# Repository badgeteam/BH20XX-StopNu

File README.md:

# Bornhack StopNu project page

For the Bornhack hacker camp we want to build a traffic light system for the
main entrance. The details are still being worked out. This archive will
contain a description and design of all the complete project.

The software repository can be found here:  
https://github.com/badgeteam/stopnu-firmware

The design of the main control board can be found here:
https://github.com/badgeteam/stopnu-hardware

# Directory structure

 * ./documentation: documentation we write and use for designing the StopNu.
 * ./electronics: Wiring and used off the shelf electronic components. 
 * ./mechanical: Mechanical design files and drawings. 
 * ./photos: Photos used to illustrate the design.
 * ./pcb_light: The design of the LED panel (schematic and PCB, CadSoft Eagle and PDF)
# License 

The hardware design is licenced under the "CERN Open Hardware Licence Version 2 - Permissive".

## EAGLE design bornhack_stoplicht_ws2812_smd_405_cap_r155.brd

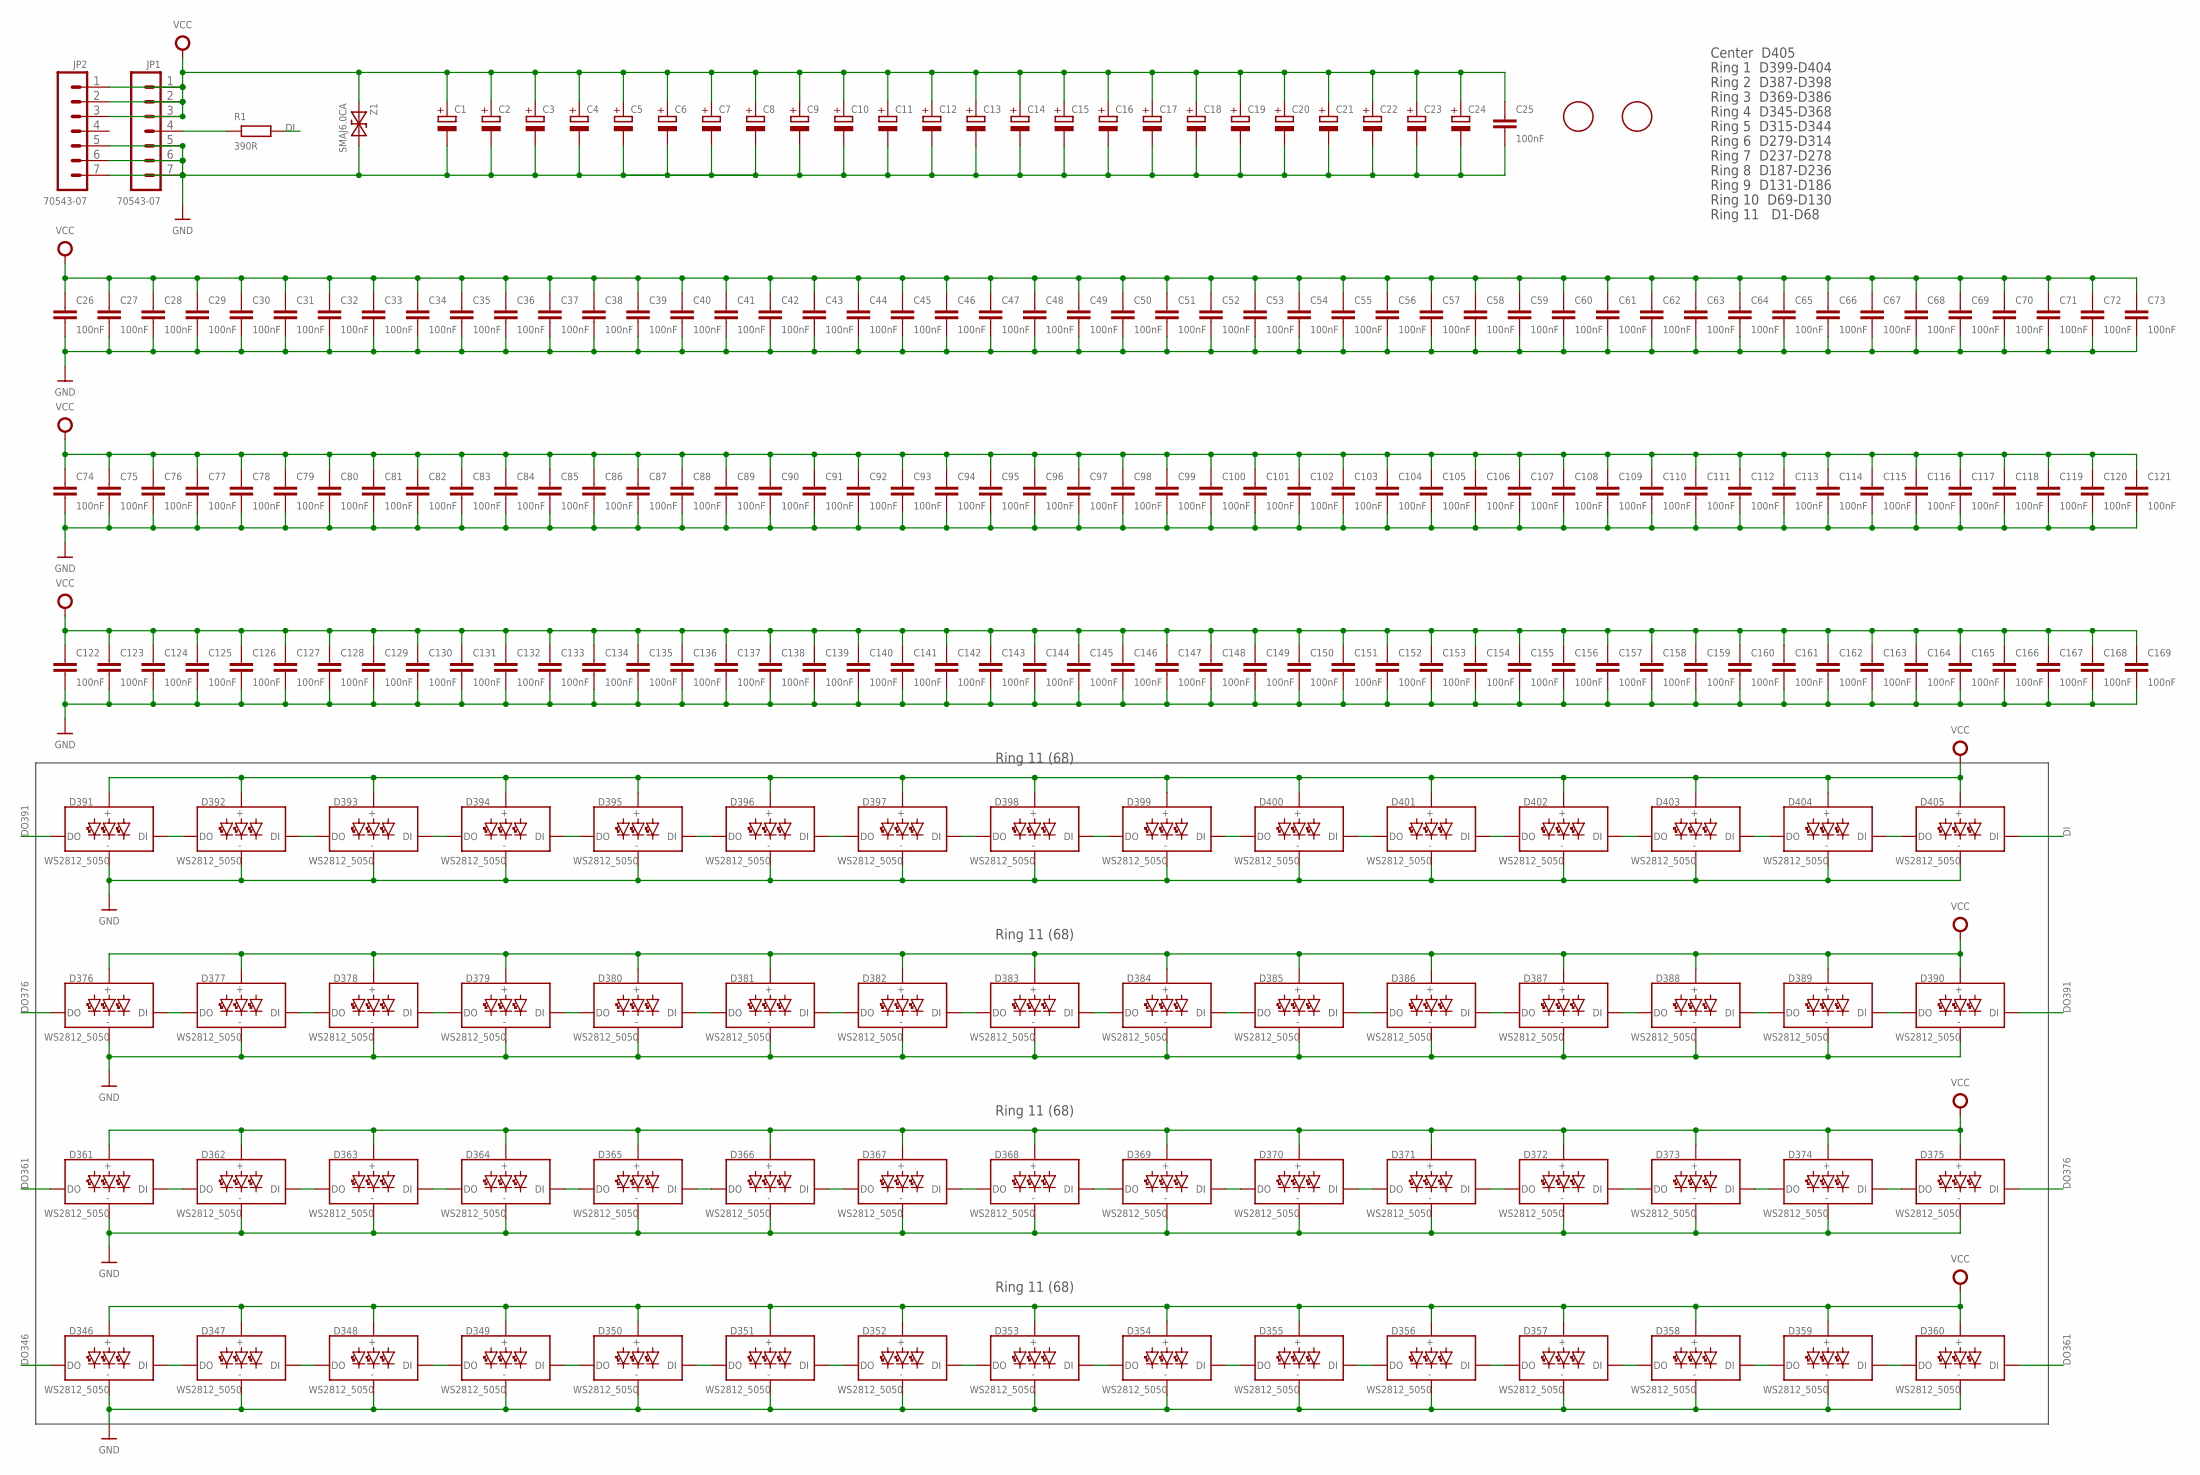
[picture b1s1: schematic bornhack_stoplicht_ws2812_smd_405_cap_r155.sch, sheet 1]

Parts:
C1, C2, C3, C4, C5, C6, C7, C8, C9, C10, C11, C12, C13, C14, C15, C16, C17, C18, C19, C20, C21, C22, C23, C24: CPOL-EUE2.5-6; E2,5-6
C25, C26, C27, C28, C29, C30, C31, C32, C33, C34, C35, C36, C37, C38, C39, C40, C41, C42, C43, C44, C45, C46, C47, C48, C49, C50, C51, C52, C53, C54, C55, C56, C57, C58, C59, C60, C61, C62, C63, C64, C65, C66, C67, C68, C69, C70, C71, C72, C73, C74, C75, C76, C77, C78, C79, C80, C81, C82, C83, C84, C85, C86, C87, C88, C89, C90, C91, C92, C93, C94, C95, C96, C97, C98, C99, C100, C101, C102, C103, C104, C105, C106, C107, C108, C109, C110, C111, C112, C113, C114, C115, C116, C117, C118, C119, C120, C121, C122, C123, C124, C125, C126, C127, C128, C129, C130, C131, C132, C133, C134, C135, C136, C137, C138, C139, C140, C141, C142, C143, C144, C145, C146, C147, C148, C149, C150, C151, C152, C153, C154, C155, C156, C157, C158, C159, C160, C161, C162, C163, C164, C165, C166, C167, C168, C169: 100nF; C0603K
D346, D347, D348, D349, D350, D351, D352, D353, D354, D355, D356, D357, D358, D359, D360, D361, D362, D363, D364, D365, D366, D367, D368, D369, D370, D371, D372, D373, D374, D375, D376, D377, D378, D379, D380, D381, D382, D383, D384, D385, D386, D387, D388, D389, D390, D391, D392, D393, D394, D395, D396, D397, D398, D399, D400, D401, D402, D403, D404, D405: WS2812_5050; WS2812-5X5-4PIN
JP1, JP2: 70543-07
R1: 390R; R0805
U2, U4: FIDUCIAL; FIDUCIAL_1MM
Z1: SMAJ6.0CA; DO214AC

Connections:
DI: D405.DI, R1.2
DO346: D346.DO; also elsewhere on the board
DO347: D346.DI, D347.DO
DO348: D347.DI, D348.DO
DO349: D348.DI, D349.DO
DO350: D349.DI, D350.DO
DO351: D350.DI, D351.DO
DO352: D351.DI, D352.DO
DO353: D352.DI, D353.DO
DO354: D353.DI, D354.DO
DO355: D354.DI, D355.DO
DO356: D355.DI, D356.DO
DO357: D356.DI, D357.DO
DO358: D357.DI, D358.DO
DO359: D358.DI, D359.DO
DO360: D359.DI, D360.DO
DO361: D360.DI, D361.DO
DO362: D361.DI, D362.DO
DO363: D362.DI, D363.DO
DO364: D363.DI, D364.DO
DO365: D364.DI, D365.DO
DO366: D365.DI, D366.DO
DO367: D366.DI, D367.DO
DO368: D367.DI, D368.DO
DO369: D368.DI, D369.DO
DO370: D369.DI, D370.DO
DO371: D370.DI, D371.DO
DO372: D371.DI, D372.DO
DO373: D372.DI, D373.DO
DO374: D373.DI, D374.DO
DO375: D374.DI, D375.DO
DO376: D375.DI, D376.DO
DO377: D376.DI, D377.DO
DO378: D377.DI, D378.DO
DO379: D378.DI, D379.DO
DO380: D379.DI, D380.DO
DO381: D380.DI, D381.DO
DO382: D381.DI, D382.DO
DO383: D382.DI, D383.DO
DO384: D383.DI, D384.DO
DO385: D384.DI, D385.DO
DO386: D385.DI, D386.DO
DO387: D386.DI, D387.DO
DO388: D387.DI, D388.DO
DO389: D388.DI, D389.DO
DO390: D389.DI, D390.DO
DO391: D390.DI, D391.DO
DO392: D391.DI, D392.DO
DO393: D392.DI, D393.DO
DO394: D393.DI, D394.DO
DO395: D394.DI, D395.DO
DO396: D395.DI, D396.DO
DO397: D396.DI, D397.DO
DO398: D397.DI, D398.DO
DO399: D398.DI, D399.DO
DO400: D399.DI, D400.DO
DO401: D400.DI, D401.DO
DO402: D401.DI, D402.DO
DO403: D402.DI, D403.DO
DO404: D403.DI, D404.DO
DO405: D404.DI, D405.DO
GND: C1.-, C2.-, C3.-, C4.-, C5.-, C6.-, C7.-, C8.-, C9.-, C10.-, C11.-, C12.-, C13.-, C14.-, C15.-, C16.-, C17.-, C18.-, C19.-, C20.-, C21.-, C22.-, C23.-, C24.-, C25.2, C26.2, C27.2, C28.2, C29.2, C30.2, C31.2, C32.2, C33.2, C34.2, C35.2, C36.2, C37.2, C38.2, C39.2, C40.2, C41.2, C42.2, C43.2, C44.2, C45.2, C46.2, C47.2, C48.2, C49.2, C50.2, C51.2, C52.2, C53.2, C54.2, C55.2, C56.2, C57.2, C58.2, C59.2, C60.2, C61.2, C62.2, C63.2, C64.2, C65.2, C66.2, C67.2, C68.2, C69.2, C70.2, C71.2, C72.2, C73.2, C74.2, C75.2, C76.2, C77.2, C78.2, C79.2, C80.2, C81.2, C82.2, C83.2, C84.2, C85.2, C86.2, C87.2, C88.2, C89.2, C90.2, C91.2, C92.2, C93.2, C94.2, C95.2, C96.2, C97.2, C98.2, C99.2, C100.2, C101.2, C102.2, C103.2, C104.2, C105.2, C106.2, C107.2, C108.2, C109.2, C110.2, C111.2, C112.2, C113.2, C114.2, C115.2, C116.2, C117.2, C118.2, C119.2, C120.2, C121.2, C122.2, C123.2, C124.2, C125.2, C126.2, C127.2, C128.2, C129.2, C130.2, C131.2, C132.2, C133.2, C134.2, C135.2, C136.2, C137.2, C138.2, C139.2, C140.2, C141.2, C142.2, C143.2, C144.2, C145.2, C146.2, C147.2, C148.2, C149.2, C150.2, C151.2, C152.2, C153.2, C154.2, C155.2, C156.2, C157.2, C158.2, C159.2, C160.2, C161.2, C162.2, C163.2, C164.2, C165.2, C166.2, C167.2, C168.2, C169.2, D346.GND, D347.GND, D348.GND, D349.GND, D350.GND, D351.GND, D352.GND, D353.GND, D354.GND, D355.GND, D356.GND, D357.GND, D358.GND, D359.GND, D360.GND, D361.GND, D362.GND, D363.GND, D364.GND, D365.GND, D366.GND, D367.GND, D368.GND, D369.GND, D370.GND, D371.GND, D372.GND, D373.GND, D374.GND, D375.GND, D376.GND, D377.GND, D378.GND, D379.GND, D380.GND, D381.GND, D382.GND, D383.GND, D384.GND, D385.GND, D386.GND, D387.GND, D388.GND, D389.GND, D390.GND, D391.GND, D392.GND, D393.GND, D394.GND, D395.GND, D396.GND, D397.GND, D398.GND, D399.GND, D400.GND, D401.GND, D402.GND, D403.GND, D404.GND, D405.GND, JP1.5, JP1.6, JP1.7, JP2.5, JP2.6, JP2.7, Z1.2; also elsewhere on the board
IN: JP1.4, R1.1
VCC: C1.+, C2.+, C3.+, C4.+, C5.+, C6.+, C7.+, C8.+, C9.+, C10.+, C11.+, C12.+, C13.+, C14.+, C15.+, C16.+, C17.+, C18.+, C19.+, C20.+, C21.+, C22.+, C23.+, C24.+, C25.1, C26.1, C27.1, C28.1, C29.1, C30.1, C31.1, C32.1, C33.1, C34.1, C35.1, C36.1, C37.1, C38.1, C39.1, C40.1, C41.1, C42.1, C43.1, C44.1, C45.1, C46.1, C47.1, C48.1, C49.1, C50.1, C51.1, C52.1, C53.1, C54.1, C55.1, C56.1, C57.1, C58.1, C59.1, C60.1, C61.1, C62.1, C63.1, C64.1, C65.1, C66.1, C67.1, C68.1, C69.1, C70.1, C71.1, C72.1, C73.1, C74.1, C75.1, C76.1, C77.1, C78.1, C79.1, C80.1, C81.1, C82.1, C83.1, C84.1, C85.1, C86.1, C87.1, C88.1, C89.1, C90.1, C91.1, C92.1, C93.1, C94.1, C95.1, C96.1, C97.1, C98.1, C99.1, C100.1, C101.1, C102.1, C103.1, C104.1, C105.1, C106.1, C107.1, C108.1, C109.1, C110.1, C111.1, C112.1, C113.1, C114.1, C115.1, C116.1, C117.1, C118.1, C119.1, C120.1, C121.1, C122.1, C123.1, C124.1, C125.1, C126.1, C127.1, C128.1, C129.1, C130.1, C131.1, C132.1, C133.1, C134.1, C135.1, C136.1, C137.1, C138.1, C139.1, C140.1, C141.1, C142.1, C143.1, C144.1, C145.1, C146.1, C147.1, C148.1, C149.1, C150.1, C151.1, C152.1, C153.1, C154.1, C155.1, C156.1, C157.1, C158.1, C159.1, C160.1, C161.1, C162.1, C163.1, C164.1, C165.1, C166.1, C167.1, C168.1, C169.1, D346.VCC, D347.VCC, D348.VCC, D349.VCC, D350.VCC, D351.VCC, D352.VCC, D353.VCC, D354.VCC, D355.VCC, D356.VCC, D357.VCC, D358.VCC, D359.VCC, D360.VCC, D361.VCC, D362.VCC, D363.VCC, D364.VCC, D365.VCC, D366.VCC, D367.VCC, D368.VCC, D369.VCC, D370.VCC, D371.VCC, D372.VCC, D373.VCC, D374.VCC, D375.VCC, D376.VCC, D377.VCC, D378.VCC, D379.VCC, D380.VCC, D381.VCC, D382.VCC, D383.VCC, D384.VCC, D385.VCC, D386.VCC, D387.VCC, D388.VCC, D389.VCC, D390.VCC, D391.VCC, D392.VCC, D393.VCC, D394.VCC, D395.VCC, D396.VCC, D397.VCC, D398.VCC, D399.VCC, D400.VCC, D401.VCC, D402.VCC, D403.VCC, D404.VCC, D405.VCC, JP1.1, JP1.2, JP1.3, JP2.1, JP2.2, JP2.3, Z1.1; also elsewhere on the board

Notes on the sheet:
Ring 11 (68)
Center D405
Ring 1 D399-D404
Ring 2 D387-D398
Ring 3 D369-D386
Ring 4 D345-D368
Ring 5 D315-D344
Ring 6 D279-D314
Ring 7 D237-D278
Ring 8 D187-D236
Ring 9 D131-D186
Ring 10 D69-D130
Ring 11 D1-D68

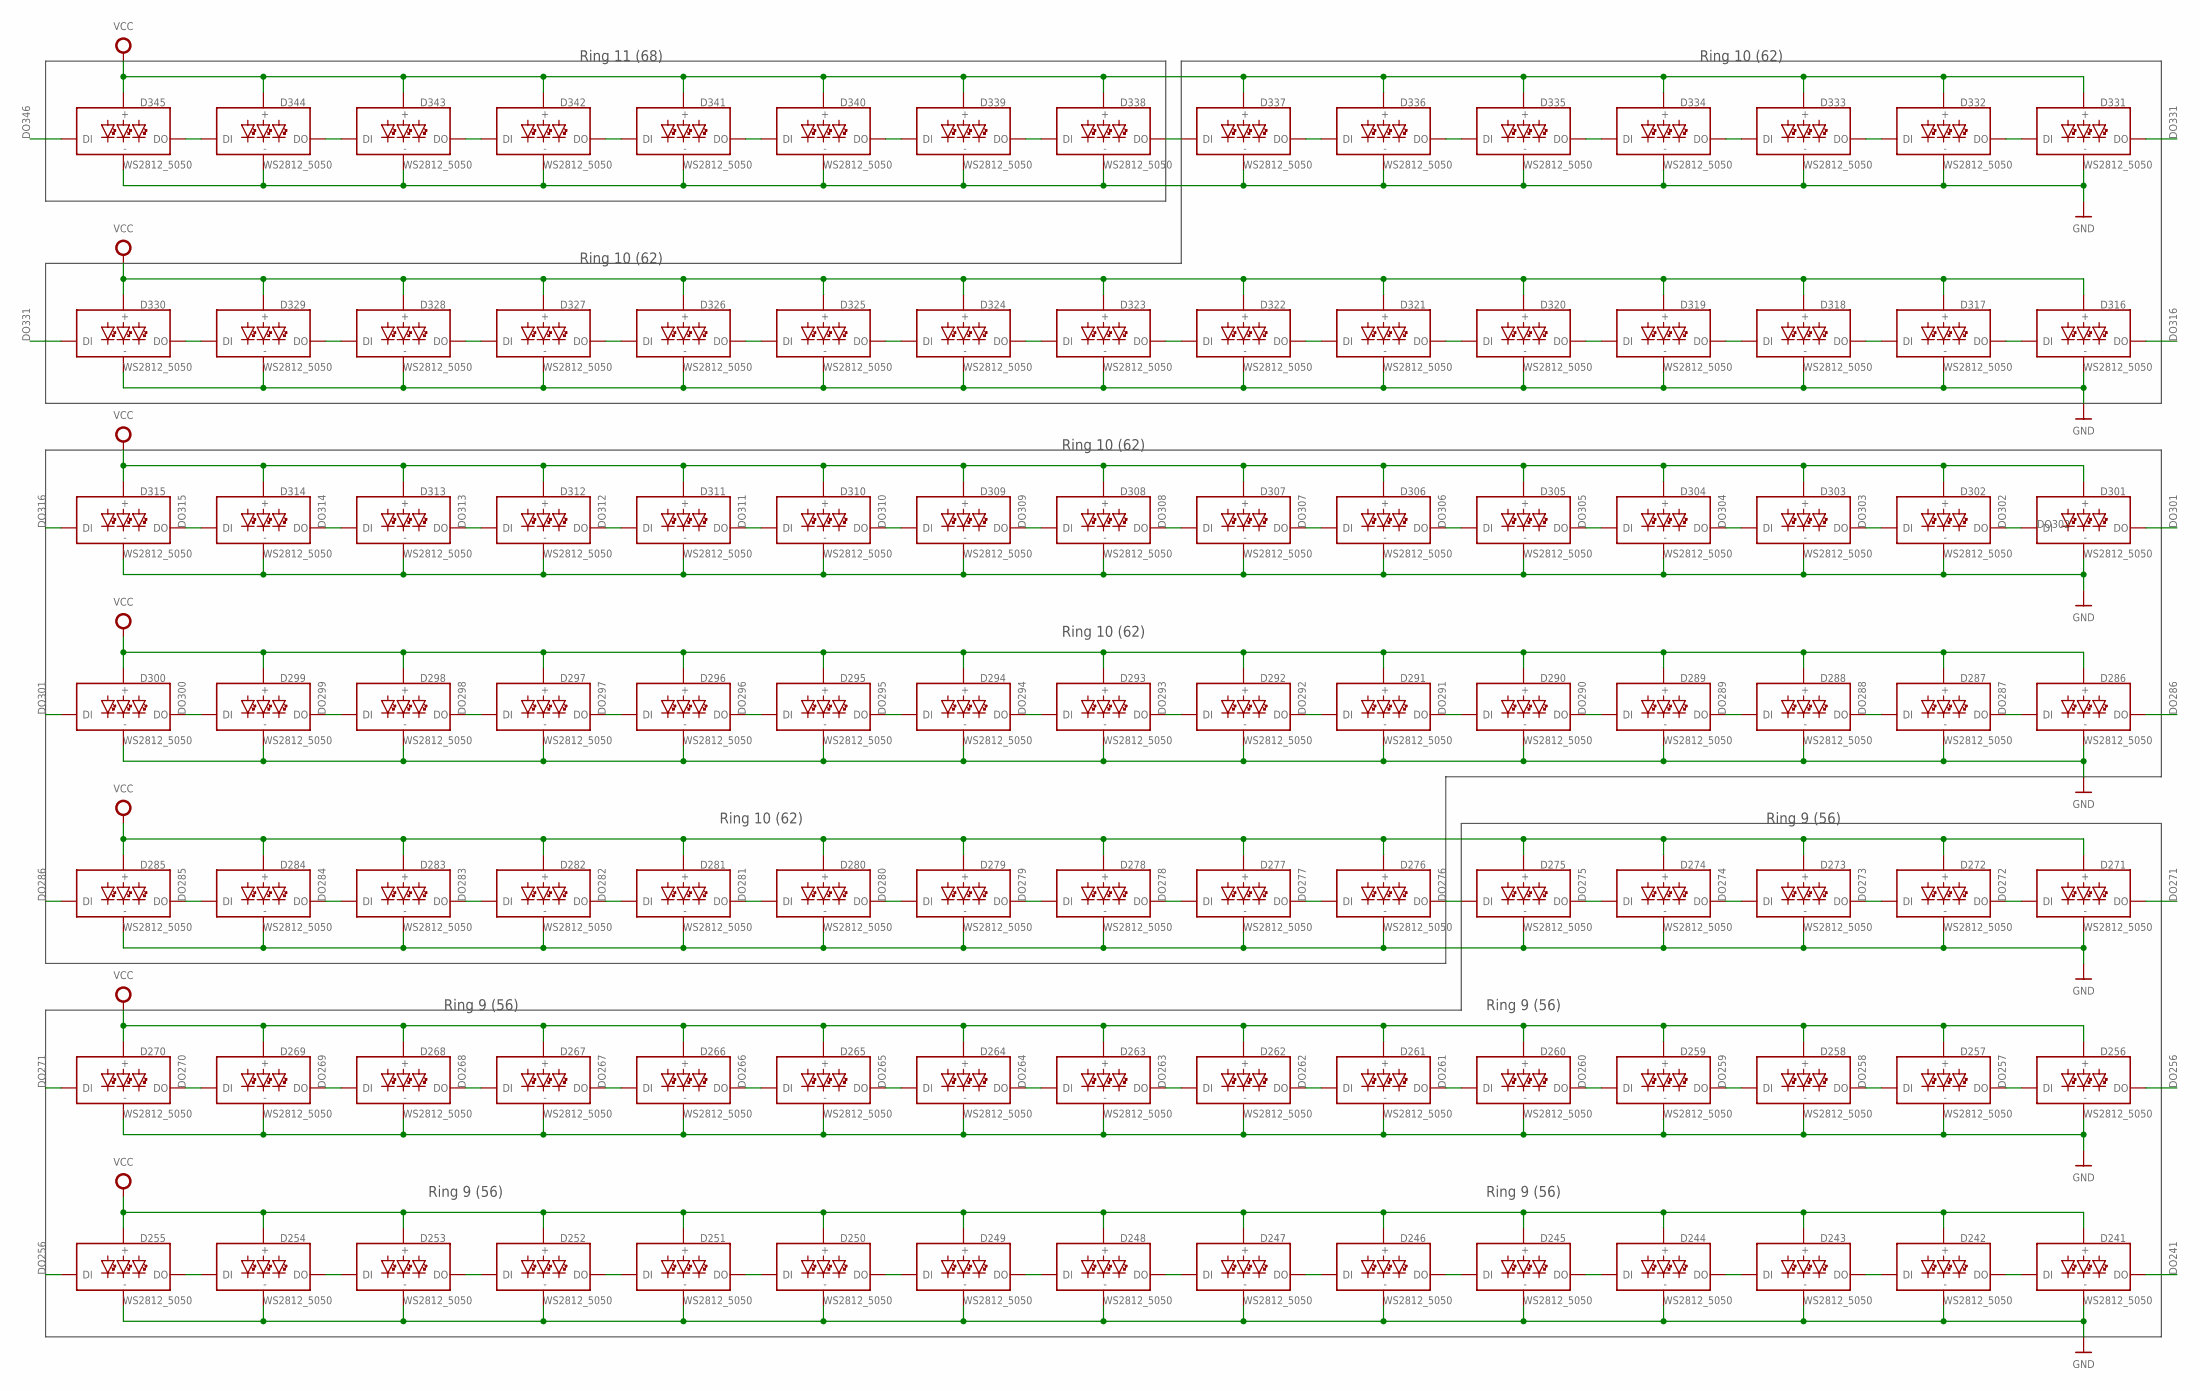
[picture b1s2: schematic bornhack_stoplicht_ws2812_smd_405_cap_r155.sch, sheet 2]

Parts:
D241, D242, D243, D244, D245, D246, D247, D248, D249, D250, D251, D252, D253, D254, D255, D256, D257, D258, D259, D260, D261, D262, D263, D264, D265, D266, D267, D268, D269, D270, D271, D272, D273, D274, D275, D276, D277, D278, D279, D280, D281, D282, D283, D284, D285, D286, D287, D288, D289, D290, D291, D292, D293, D294, D295, D296, D297, D298, D299, D300, D301, D302, D303, D304, D305, D306, D307, D308, D309, D310, D311, D312, D313, D314, D315, D316, D317, D318, D319, D320, D321, D322, D323, D324, D325, D326, D327, D328, D329, D330, D331, D332, D333, D334, D335, D336, D337, D338, D339, D340, D341, D342, D343, D344, D345: WS2812_5050; WS2812-5X5-4PIN

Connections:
DO241: D241.DO; also elsewhere on the board
DO242: D241.DI, D242.DO
DO243: D242.DI, D243.DO
DO244: D243.DI, D244.DO
DO245: D244.DI, D245.DO
DO246: D245.DI, D246.DO
DO247: D246.DI, D247.DO
DO248: D247.DI, D248.DO
DO249: D248.DI, D249.DO
DO250: D249.DI, D250.DO
DO251: D250.DI, D251.DO
DO252: D251.DI, D252.DO
DO253: D252.DI, D253.DO
DO254: D253.DI, D254.DO
DO255: D254.DI, D255.DO
DO256: D255.DI, D256.DO
DO257: D256.DI, D257.DO
DO258: D257.DI, D258.DO
DO259: D258.DI, D259.DO
DO260: D259.DI, D260.DO
DO261: D260.DI, D261.DO
DO262: D261.DI, D262.DO
DO263: D262.DI, D263.DO
DO264: D263.DI, D264.DO
DO265: D264.DI, D265.DO
DO266: D265.DI, D266.DO
DO267: D266.DI, D267.DO
DO268: D267.DI, D268.DO
DO269: D268.DI, D269.DO
DO270: D269.DI, D270.DO
DO271: D270.DI, D271.DO
DO272: D271.DI, D272.DO
DO273: D272.DI, D273.DO
DO274: D273.DI, D274.DO
DO275: D274.DI, D275.DO
DO276: D275.DI, D276.DO
DO277: D276.DI, D277.DO
DO278: D277.DI, D278.DO
DO279: D278.DI, D279.DO
DO280: D279.DI, D280.DO
DO281: D280.DI, D281.DO
DO282: D281.DI, D282.DO
DO283: D282.DI, D283.DO
DO284: D283.DI, D284.DO
DO285: D284.DI, D285.DO
DO286: D285.DI, D286.DO
DO287: D286.DI, D287.DO
DO288: D287.DI, D288.DO
DO289: D288.DI, D289.DO
DO290: D289.DI, D290.DO
DO291: D290.DI, D291.DO
DO292: D291.DI, D292.DO
DO293: D292.DI, D293.DO
DO294: D293.DI, D294.DO
DO295: D294.DI, D295.DO
DO296: D295.DI, D296.DO
DO297: D296.DI, D297.DO
DO298: D297.DI, D298.DO
DO299: D298.DI, D299.DO
DO300: D299.DI, D300.DO
DO301: D300.DI, D301.DO
DO302: D301.DI, D302.DO
DO303: D302.DI, D303.DO
DO304: D303.DI, D304.DO
DO305: D304.DI, D305.DO
DO306: D305.DI, D306.DO
DO307: D306.DI, D307.DO
DO308: D307.DI, D308.DO
DO309: D308.DI, D309.DO
DO310: D309.DI, D310.DO
DO311: D310.DI, D311.DO
DO312: D311.DI, D312.DO
DO313: D312.DI, D313.DO
DO314: D313.DI, D314.DO
DO315: D314.DI, D315.DO
DO316: D315.DI, D316.DO
DO317: D316.DI, D317.DO
DO318: D317.DI, D318.DO
DO319: D318.DI, D319.DO
DO320: D319.DI, D320.DO
DO321: D320.DI, D321.DO
DO322: D321.DI, D322.DO
DO323: D322.DI, D323.DO
DO324: D323.DI, D324.DO
DO325: D324.DI, D325.DO
DO326: D325.DI, D326.DO
DO327: D326.DI, D327.DO
DO328: D327.DI, D328.DO
DO329: D328.DI, D329.DO
DO330: D329.DI, D330.DO
DO331: D330.DI, D331.DO
DO332: D331.DI, D332.DO
DO333: D332.DI, D333.DO
DO334: D333.DI, D334.DO
DO335: D334.DI, D335.DO
DO336: D335.DI, D336.DO
DO337: D336.DI, D337.DO
DO338: D337.DI, D338.DO
DO339: D338.DI, D339.DO
DO340: D339.DI, D340.DO
DO341: D340.DI, D341.DO
DO342: D341.DI, D342.DO
DO343: D342.DI, D343.DO
DO344: D343.DI, D344.DO
DO345: D344.DI, D345.DO
DO346: D345.DI; also elsewhere on the board
GND: D241.GND, D242.GND, D243.GND, D244.GND, D245.GND, D246.GND, D247.GND, D248.GND, D249.GND, D250.GND, D251.GND, D252.GND, D253.GND, D254.GND, D255.GND, D256.GND, D257.GND, D258.GND, D259.GND, D260.GND, D261.GND, D262.GND, D263.GND, D264.GND, D265.GND, D266.GND, D267.GND, D268.GND, D269.GND, D270.GND, D271.GND, D272.GND, D273.GND, D274.GND, D275.GND, D276.GND, D277.GND, D278.GND, D279.GND, D280.GND, D281.GND, D282.GND, D283.GND, D284.GND, D285.GND, D286.GND, D287.GND, D288.GND, D289.GND, D290.GND, D291.GND, D292.GND, D293.GND, D294.GND, D295.GND, D296.GND, D297.GND, D298.GND, D299.GND, D300.GND, D301.GND, D302.GND, D303.GND, D304.GND, D305.GND, D306.GND, D307.GND, D308.GND, D309.GND, D310.GND, D311.GND, D312.GND, D313.GND, D314.GND, D315.GND, D316.GND, D317.GND, D318.GND, D319.GND, D320.GND, D321.GND, D322.GND, D323.GND, D324.GND, D325.GND, D326.GND, D327.GND, D328.GND, D329.GND, D330.GND, D331.GND, D332.GND, D333.GND, D334.GND, D335.GND, D336.GND, D337.GND, D338.GND, D339.GND, D340.GND, D341.GND, D342.GND, D343.GND, D344.GND, D345.GND; also elsewhere on the board
VCC: D241.VCC, D242.VCC, D243.VCC, D244.VCC, D245.VCC, D246.VCC, D247.VCC, D248.VCC, D249.VCC, D250.VCC, D251.VCC, D252.VCC, D253.VCC, D254.VCC, D255.VCC, D256.VCC, D257.VCC, D258.VCC, D259.VCC, D260.VCC, D261.VCC, D262.VCC, D263.VCC, D264.VCC, D265.VCC, D266.VCC, D267.VCC, D268.VCC, D269.VCC, D270.VCC, D271.VCC, D272.VCC, D273.VCC, D274.VCC, D275.VCC, D276.VCC, D277.VCC, D278.VCC, D279.VCC, D280.VCC, D281.VCC, D282.VCC, D283.VCC, D284.VCC, D285.VCC, D286.VCC, D287.VCC, D288.VCC, D289.VCC, D290.VCC, D291.VCC, D292.VCC, D293.VCC, D294.VCC, D295.VCC, D296.VCC, D297.VCC, D298.VCC, D299.VCC, D300.VCC, D301.VCC, D302.VCC, D303.VCC, D304.VCC, D305.VCC, D306.VCC, D307.VCC, D308.VCC, D309.VCC, D310.VCC, D311.VCC, D312.VCC, D313.VCC, D314.VCC, D315.VCC, D316.VCC, D317.VCC, D318.VCC, D319.VCC, D320.VCC, D321.VCC, D322.VCC, D323.VCC, D324.VCC, D325.VCC, D326.VCC, D327.VCC, D328.VCC, D329.VCC, D330.VCC, D331.VCC, D332.VCC, D333.VCC, D334.VCC, D335.VCC, D336.VCC, D337.VCC, D338.VCC, D339.VCC, D340.VCC, D341.VCC, D342.VCC, D343.VCC, D344.VCC, D345.VCC; also elsewhere on the board

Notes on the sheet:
Ring 9 (56)
Ring 10 (62)
Ring 11 (68)

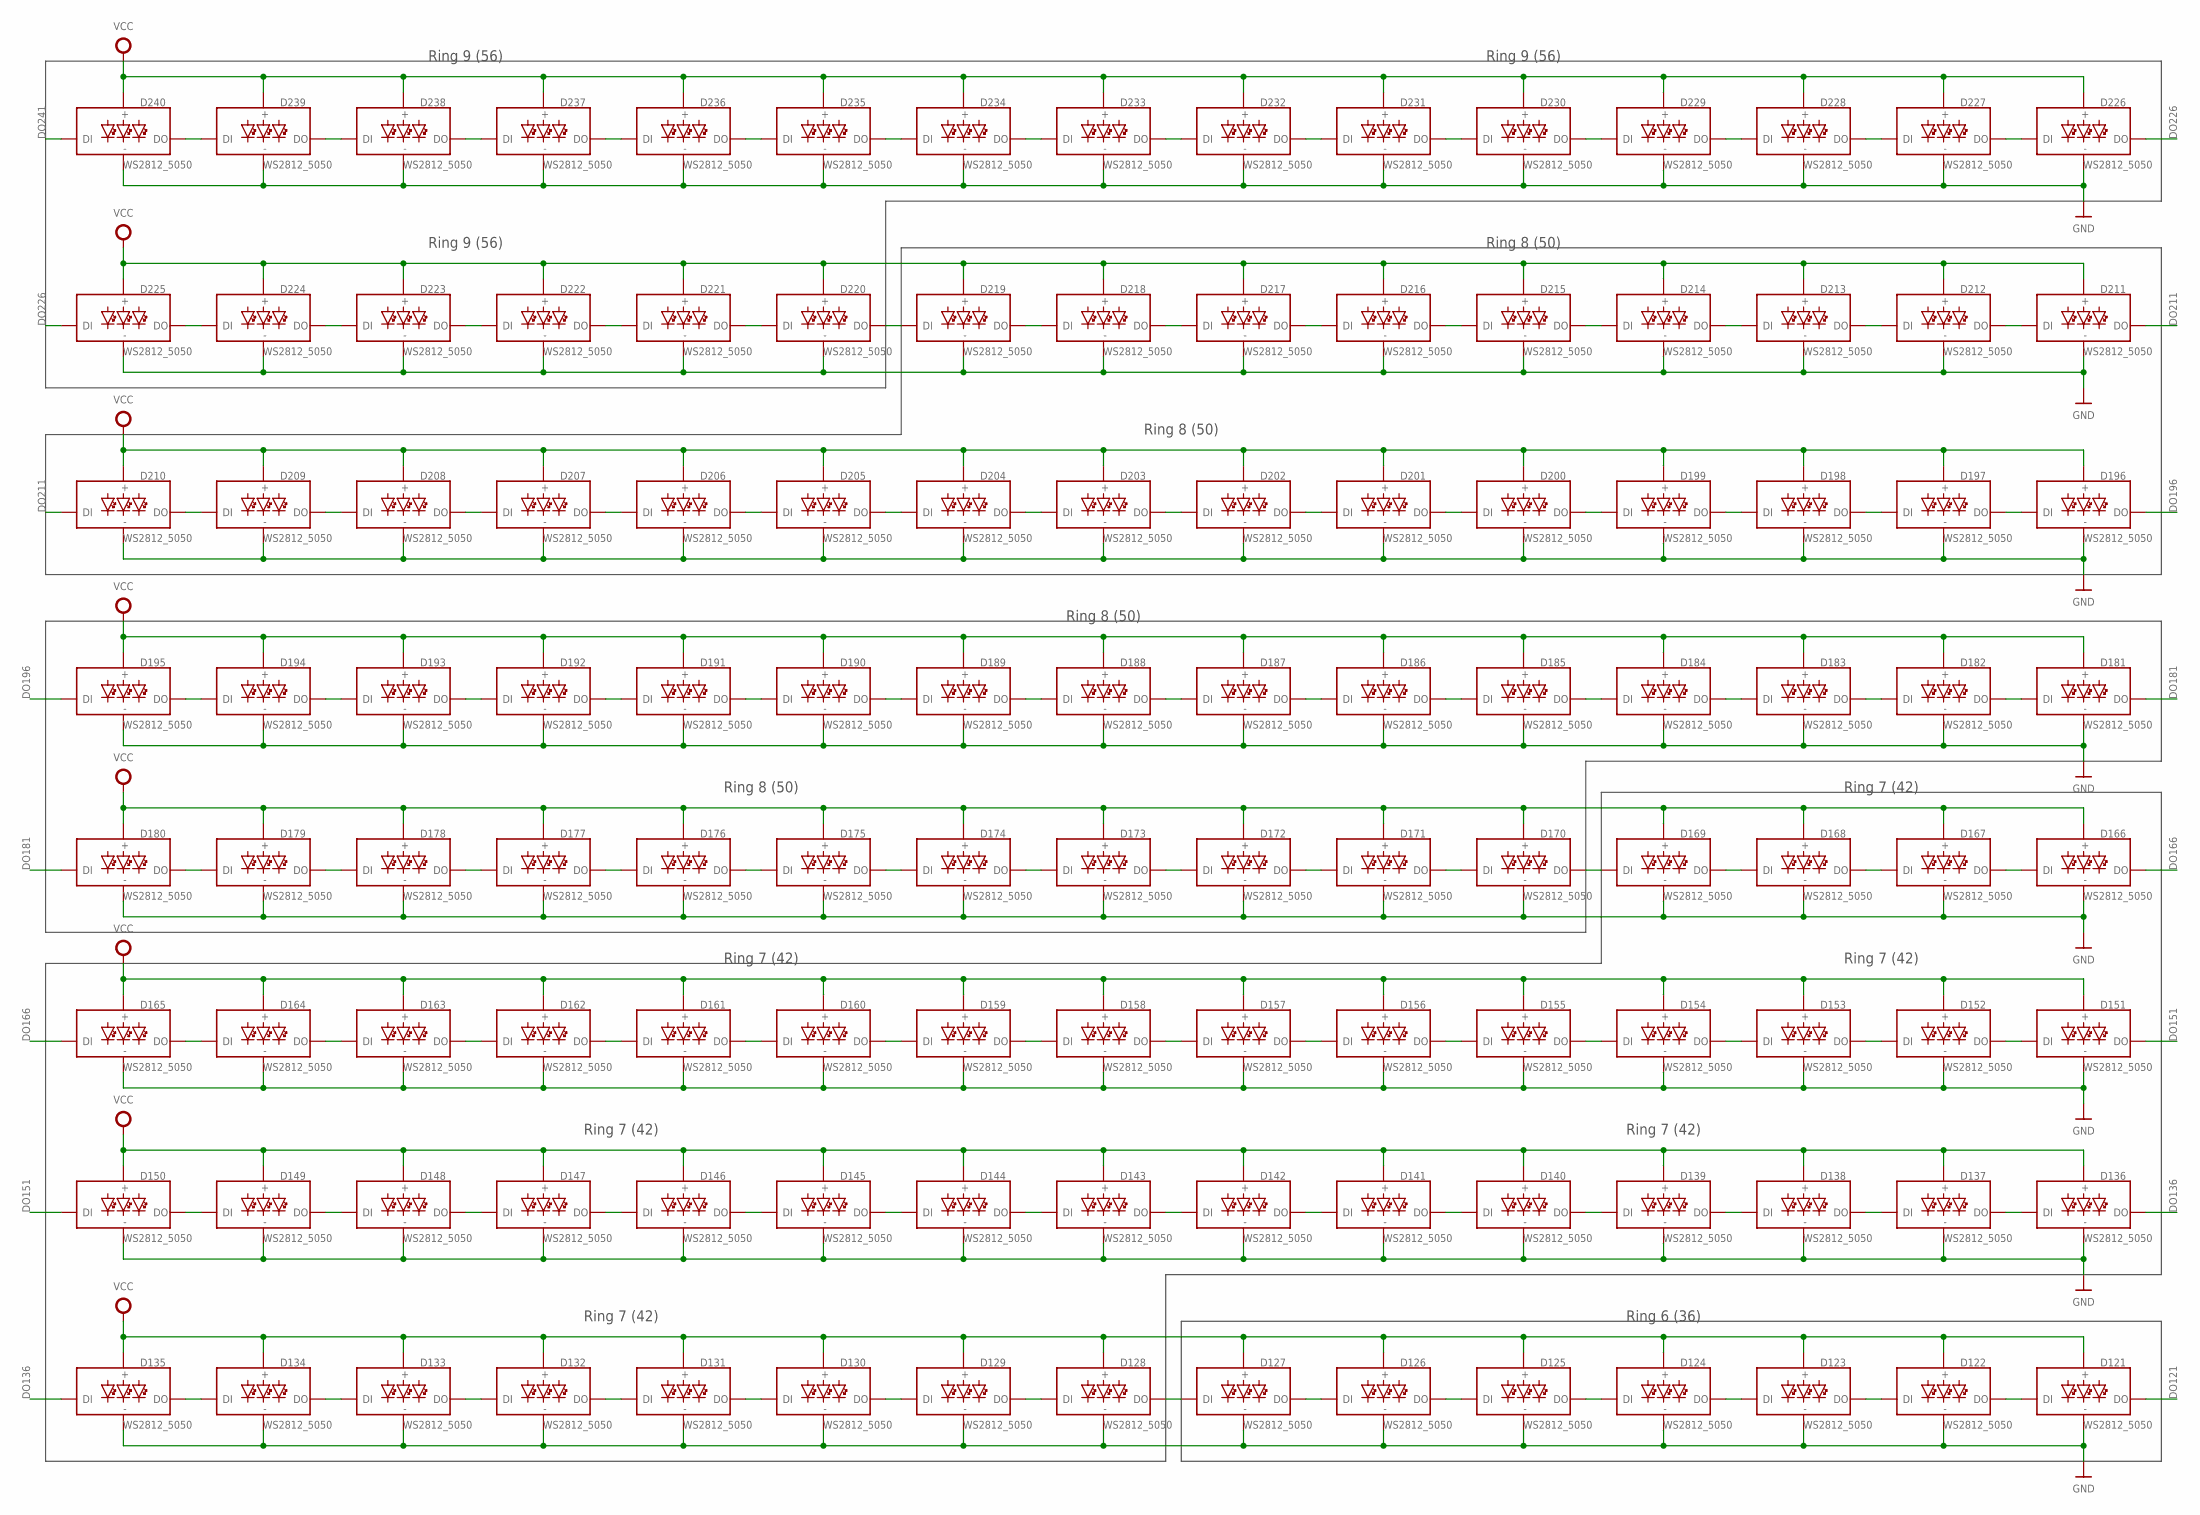
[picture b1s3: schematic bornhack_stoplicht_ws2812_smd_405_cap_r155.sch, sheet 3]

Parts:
D121, D122, D123, D124, D125, D126, D127, D128, D129, D130, D131, D132, D133, D134, D135, D136, D137, D138, D139, D140, D141, D142, D143, D144, D145, D146, D147, D148, D149, D150, D151, D152, D153, D154, D155, D156, D157, D158, D159, D160, D161, D162, D163, D164, D165, D166, D167, D168, D169, D170, D171, D172, D173, D174, D175, D176, D177, D178, D179, D180, D181, D182, D183, D184, D185, D186, D187, D188, D189, D190, D191, D192, D193, D194, D195, D196, D197, D198, D199, D200, D201, D202, D203, D204, D205, D206, D207, D208, D209, D210, D211, D212, D213, D214, D215, D216, D217, D218, D219, D220, D221, D222, D223, D224, D225, D226, D227, D228, D229, D230, D231, D232, D233, D234, D235, D236, D237, D238, D239, D240: WS2812_5050; WS2812-5X5-4PIN

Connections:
DO121: D121.DO; also elsewhere on the board
DO122: D121.DI, D122.DO
DO123: D122.DI, D123.DO
DO124: D123.DI, D124.DO
DO125: D124.DI, D125.DO
DO126: D125.DI, D126.DO
DO127: D126.DI, D127.DO
DO128: D127.DI, D128.DO
DO129: D128.DI, D129.DO
DO130: D129.DI, D130.DO
DO131: D130.DI, D131.DO
DO132: D131.DI, D132.DO
DO133: D132.DI, D133.DO
DO134: D133.DI, D134.DO
DO135: D134.DI, D135.DO
DO136: D135.DI, D136.DO
DO137: D136.DI, D137.DO
DO138: D137.DI, D138.DO
DO139: D138.DI, D139.DO
DO140: D139.DI, D140.DO
DO141: D140.DI, D141.DO
DO142: D141.DI, D142.DO
DO143: D142.DI, D143.DO
DO144: D143.DI, D144.DO
DO145: D144.DI, D145.DO
DO146: D145.DI, D146.DO
DO147: D146.DI, D147.DO
DO148: D147.DI, D148.DO
DO149: D148.DI, D149.DO
DO150: D149.DI, D150.DO
DO151: D150.DI, D151.DO
DO152: D151.DI, D152.DO
DO153: D152.DI, D153.DO
DO154: D153.DI, D154.DO
DO155: D154.DI, D155.DO
DO156: D155.DI, D156.DO
DO157: D156.DI, D157.DO
DO158: D157.DI, D158.DO
DO159: D158.DI, D159.DO
DO160: D159.DI, D160.DO
DO161: D160.DI, D161.DO
DO162: D161.DI, D162.DO
DO163: D162.DI, D163.DO
DO164: D163.DI, D164.DO
DO165: D164.DI, D165.DO
DO166: D165.DI, D166.DO
DO167: D166.DI, D167.DO
DO168: D167.DI, D168.DO
DO169: D168.DI, D169.DO
DO170: D169.DI, D170.DO
DO171: D170.DI, D171.DO
DO172: D171.DI, D172.DO
DO173: D172.DI, D173.DO
DO174: D173.DI, D174.DO
DO175: D174.DI, D175.DO
DO176: D175.DI, D176.DO
DO177: D176.DI, D177.DO
DO178: D177.DI, D178.DO
DO179: D178.DI, D179.DO
DO180: D179.DI, D180.DO
DO181: D180.DI, D181.DO
DO182: D181.DI, D182.DO
DO183: D182.DI, D183.DO
DO184: D183.DI, D184.DO
DO185: D184.DI, D185.DO
DO186: D185.DI, D186.DO
DO187: D186.DI, D187.DO
DO188: D187.DI, D188.DO
DO189: D188.DI, D189.DO
DO190: D189.DI, D190.DO
DO191: D190.DI, D191.DO
DO192: D191.DI, D192.DO
DO193: D192.DI, D193.DO
DO194: D193.DI, D194.DO
DO195: D194.DI, D195.DO
DO196: D195.DI, D196.DO
DO197: D196.DI, D197.DO
DO198: D197.DI, D198.DO
DO199: D198.DI, D199.DO
DO200: D199.DI, D200.DO
DO201: D200.DI, D201.DO
DO202: D201.DI, D202.DO
DO203: D202.DI, D203.DO
DO204: D203.DI, D204.DO
DO205: D204.DI, D205.DO
DO206: D205.DI, D206.DO
DO207: D206.DI, D207.DO
DO208: D207.DI, D208.DO
DO209: D208.DI, D209.DO
DO210: D209.DI, D210.DO
DO211: D210.DI, D211.DO
DO212: D211.DI, D212.DO
DO213: D212.DI, D213.DO
DO214: D213.DI, D214.DO
DO215: D214.DI, D215.DO
DO216: D215.DI, D216.DO
DO217: D216.DI, D217.DO
DO218: D217.DI, D218.DO
DO219: D218.DI, D219.DO
DO220: D219.DI, D220.DO
DO221: D220.DI, D221.DO
DO222: D221.DI, D222.DO
DO223: D222.DI, D223.DO
DO224: D223.DI, D224.DO
DO225: D224.DI, D225.DO
DO226: D225.DI, D226.DO
DO227: D226.DI, D227.DO
DO228: D227.DI, D228.DO
DO229: D228.DI, D229.DO
DO230: D229.DI, D230.DO
DO231: D230.DI, D231.DO
DO232: D231.DI, D232.DO
DO233: D232.DI, D233.DO
DO234: D233.DI, D234.DO
DO235: D234.DI, D235.DO
DO236: D235.DI, D236.DO
DO237: D236.DI, D237.DO
DO238: D237.DI, D238.DO
DO239: D238.DI, D239.DO
DO240: D239.DI, D240.DO
DO241: D240.DI; also elsewhere on the board
GND: D121.GND, D122.GND, D123.GND, D124.GND, D125.GND, D126.GND, D127.GND, D128.GND, D129.GND, D130.GND, D131.GND, D132.GND, D133.GND, D134.GND, D135.GND, D136.GND, D137.GND, D138.GND, D139.GND, D140.GND, D141.GND, D142.GND, D143.GND, D144.GND, D145.GND, D146.GND, D147.GND, D148.GND, D149.GND, D150.GND, D151.GND, D152.GND, D153.GND, D154.GND, D155.GND, D156.GND, D157.GND, D158.GND, D159.GND, D160.GND, D161.GND, D162.GND, D163.GND, D164.GND, D165.GND, D166.GND, D167.GND, D168.GND, D169.GND, D170.GND, D171.GND, D172.GND, D173.GND, D174.GND, D175.GND, D176.GND, D177.GND, D178.GND, D179.GND, D180.GND, D181.GND, D182.GND, D183.GND, D184.GND, D185.GND, D186.GND, D187.GND, D188.GND, D189.GND, D190.GND, D191.GND, D192.GND, D193.GND, D194.GND, D195.GND, D196.GND, D197.GND, D198.GND, D199.GND, D200.GND, D201.GND, D202.GND, D203.GND, D204.GND, D205.GND, D206.GND, D207.GND, D208.GND, D209.GND, D210.GND, D211.GND, D212.GND, D213.GND, D214.GND, D215.GND, D216.GND, D217.GND, D218.GND, D219.GND, D220.GND, D221.GND, D222.GND, D223.GND, D224.GND, D225.GND, D226.GND, D227.GND, D228.GND, D229.GND, D230.GND, D231.GND, D232.GND, D233.GND, D234.GND, D235.GND, D236.GND, D237.GND, D238.GND, D239.GND, D240.GND; also elsewhere on the board
VCC: D121.VCC, D122.VCC, D123.VCC, D124.VCC, D125.VCC, D126.VCC, D127.VCC, D128.VCC, D129.VCC, D130.VCC, D131.VCC, D132.VCC, D133.VCC, D134.VCC, D135.VCC, D136.VCC, D137.VCC, D138.VCC, D139.VCC, D140.VCC, D141.VCC, D142.VCC, D143.VCC, D144.VCC, D145.VCC, D146.VCC, D147.VCC, D148.VCC, D149.VCC, D150.VCC, D151.VCC, D152.VCC, D153.VCC, D154.VCC, D155.VCC, D156.VCC, D157.VCC, D158.VCC, D159.VCC, D160.VCC, D161.VCC, D162.VCC, D163.VCC, D164.VCC, D165.VCC, D166.VCC, D167.VCC, D168.VCC, D169.VCC, D170.VCC, D171.VCC, D172.VCC, D173.VCC, D174.VCC, D175.VCC, D176.VCC, D177.VCC, D178.VCC, D179.VCC, D180.VCC, D181.VCC, D182.VCC, D183.VCC, D184.VCC, D185.VCC, D186.VCC, D187.VCC, D188.VCC, D189.VCC, D190.VCC, D191.VCC, D192.VCC, D193.VCC, D194.VCC, D195.VCC, D196.VCC, D197.VCC, D198.VCC, D199.VCC, D200.VCC, D201.VCC, D202.VCC, D203.VCC, D204.VCC, D205.VCC, D206.VCC, D207.VCC, D208.VCC, D209.VCC, D210.VCC, D211.VCC, D212.VCC, D213.VCC, D214.VCC, D215.VCC, D216.VCC, D217.VCC, D218.VCC, D219.VCC, D220.VCC, D221.VCC, D222.VCC, D223.VCC, D224.VCC, D225.VCC, D226.VCC, D227.VCC, D228.VCC, D229.VCC, D230.VCC, D231.VCC, D232.VCC, D233.VCC, D234.VCC, D235.VCC, D236.VCC, D237.VCC, D238.VCC, D239.VCC, D240.VCC; also elsewhere on the board

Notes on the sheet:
Ring 6 (36)
Ring 7 (42)
Ring 8 (50)
Ring 9 (56)

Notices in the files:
parts and their libraries:
con-molex-c-grid: Copyright (C) 2009, Bob Starr
SparkFun-LED: Licensing: Creative Commons ShareAlike 4.0 International - https://creativecommons.org/licenses/by-sa/4.0
